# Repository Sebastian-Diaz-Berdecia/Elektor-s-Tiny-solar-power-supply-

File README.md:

# Elektor's Tiny solar power supply

Este proyecto consta de un pequeño convertidor elevador (boost) basado en el circuito integrado **AP3015** para generar una salida regulada de 3V3 a partir del voltaje de una batería recargable AA(A).

Durante el día un panel solar carga la batería y el circuito esta deshabilitado mientras que durante la noche el circuito se activa y la tensión de la batería es elevada hasta los 3V3 para alimentar algún elemento LED decorativo que puede ser empleado para iluminar un jardín durante las noches. 

Este circuito está basado en el proyecto **"Tiny solar power supply"** de Clemens Valens publicado en la revista Elektor. 

---

---

## 🔑 Caracteristicas principales

- **Convertidor DC-DC elevador de micropotencia AP3015A**
  - Voltaje de entrada bajo: típico 1.0V para el AP3015A.
  - Corriente de salida máxima de 100mA.
- **Alimentación**
  - Panel solar para cargar la batería durante el día.
  - Batería recargable AA(A) para encender la luz durante la noche.

---

## 🛠 Aplicaciones

- Iluminación nocturna decorativa para jardines.

---

## 📄 Documentación 

- [AP3015A](https://www.diodes.com/datasheet/download/AP3015.pdf)  
- [Tiny solar supply Elektor by Clemens Valens](https://www.elektormagazine.com/labs/tiny-solar-supply)  

---

## 📷 Preview

- *Esquematico:*

- *Layout a 2 capas:*

- *Capa 1:*

- *Capa 2:*

- *Modelo 3D vista frontal:*

- *Modelo 3D vista posterior:*

## 📜 License

This project is released under the **MIT License**.  
See the [LICENSE](LICENSE) file for details.

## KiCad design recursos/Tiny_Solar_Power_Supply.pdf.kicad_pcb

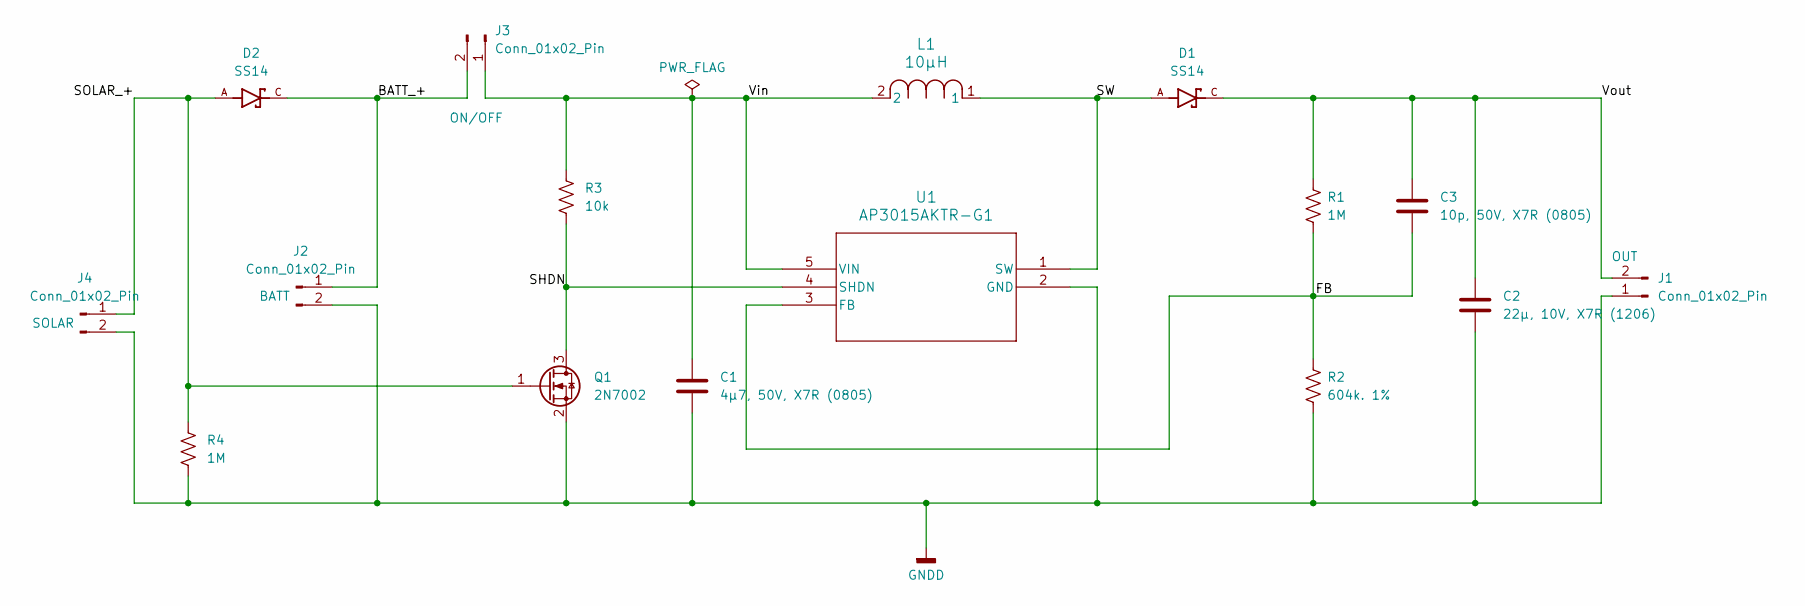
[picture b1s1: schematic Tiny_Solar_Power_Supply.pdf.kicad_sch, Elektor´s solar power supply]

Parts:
C1: 4μ7, 50V, X7R (0805); C_0805_2012Metric
C2: 22μ, 10V, X7R (1206); C_1206_3216Metric
C3: 10p, 50V, X7R (0805); C_0805_2012Metric_Pad1.18x1.45mm_HandSolder
D1, D2: SS14; DIOM4325X250N; PARTREV O2102
J1, J2, J3: Conn_01x02_Pin; PinHeader_1x02_P2.54mm_Vertical
J4: Conn_01x02_Pin; PinHeader_1x02_P2.54mm_Horizontal
L1: 10μH; IND_ASPI-0630LR_ABR
Q1: 2N7002; SOT-23
R1, R4: 1M; R_0805_2012Metric_Pad1.20x1.40mm_HandSolder
R2: 604k. 1%; R_0805_2012Metric_Pad1.20x1.40mm_HandSolder
R3: 10k; R_0805_2012Metric_Pad1.20x1.40mm_HandSolder
U1: AP3015AKTR-G1; SOT23-5_1P55X2P9_DIO

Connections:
/BATT_+: D2.C, J2.1, J3.2
/FB: C3.2, R1.1, R2.2, U1.3 (FB)
/SHDN: Q1.3 (D), R3.2, U1.4 (SHDN)
/SOLAR_+: D2.A, J4.1, Q1.1 (G), R4.1
/SW: D1.A, L1.1, U1.1 (SW)
/Vin: C1.1, J3.1, L1.2, R3.1, U1.5 (VIN)
/Vout: C2.1, C3.1, D1.C, J1.2, R1.2
GNDD: C1.2, C2.2, J1.1, J2.2, J4.2, Q1.2 (S), R2.1, R4.2, U1.2 (GND)

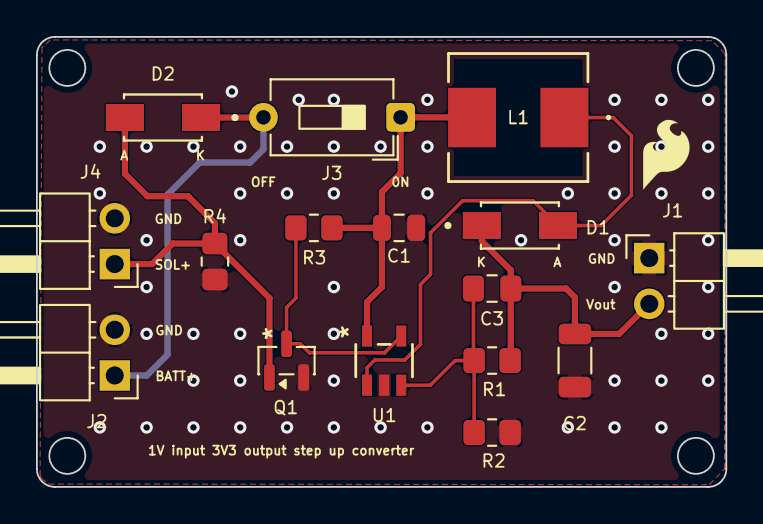
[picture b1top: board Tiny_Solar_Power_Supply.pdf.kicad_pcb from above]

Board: 2 copper layers, 38.3 x 25.0 mm, 16 parts (0 on the bottom side), 8 nets.
